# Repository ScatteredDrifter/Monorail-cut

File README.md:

# Monorail V2

This board adapts the original **Monorail V²** however some fundamental changes were made to fit into a different case by **M4NU**.

## Current status:

>Prototypes were ordered and are functioning. 

- + Encoder works 
- + VIAL firmware works 
- + LED-Backlight works
- - misconfigured stabilizer orientation. This has been fixed in 9eb0997

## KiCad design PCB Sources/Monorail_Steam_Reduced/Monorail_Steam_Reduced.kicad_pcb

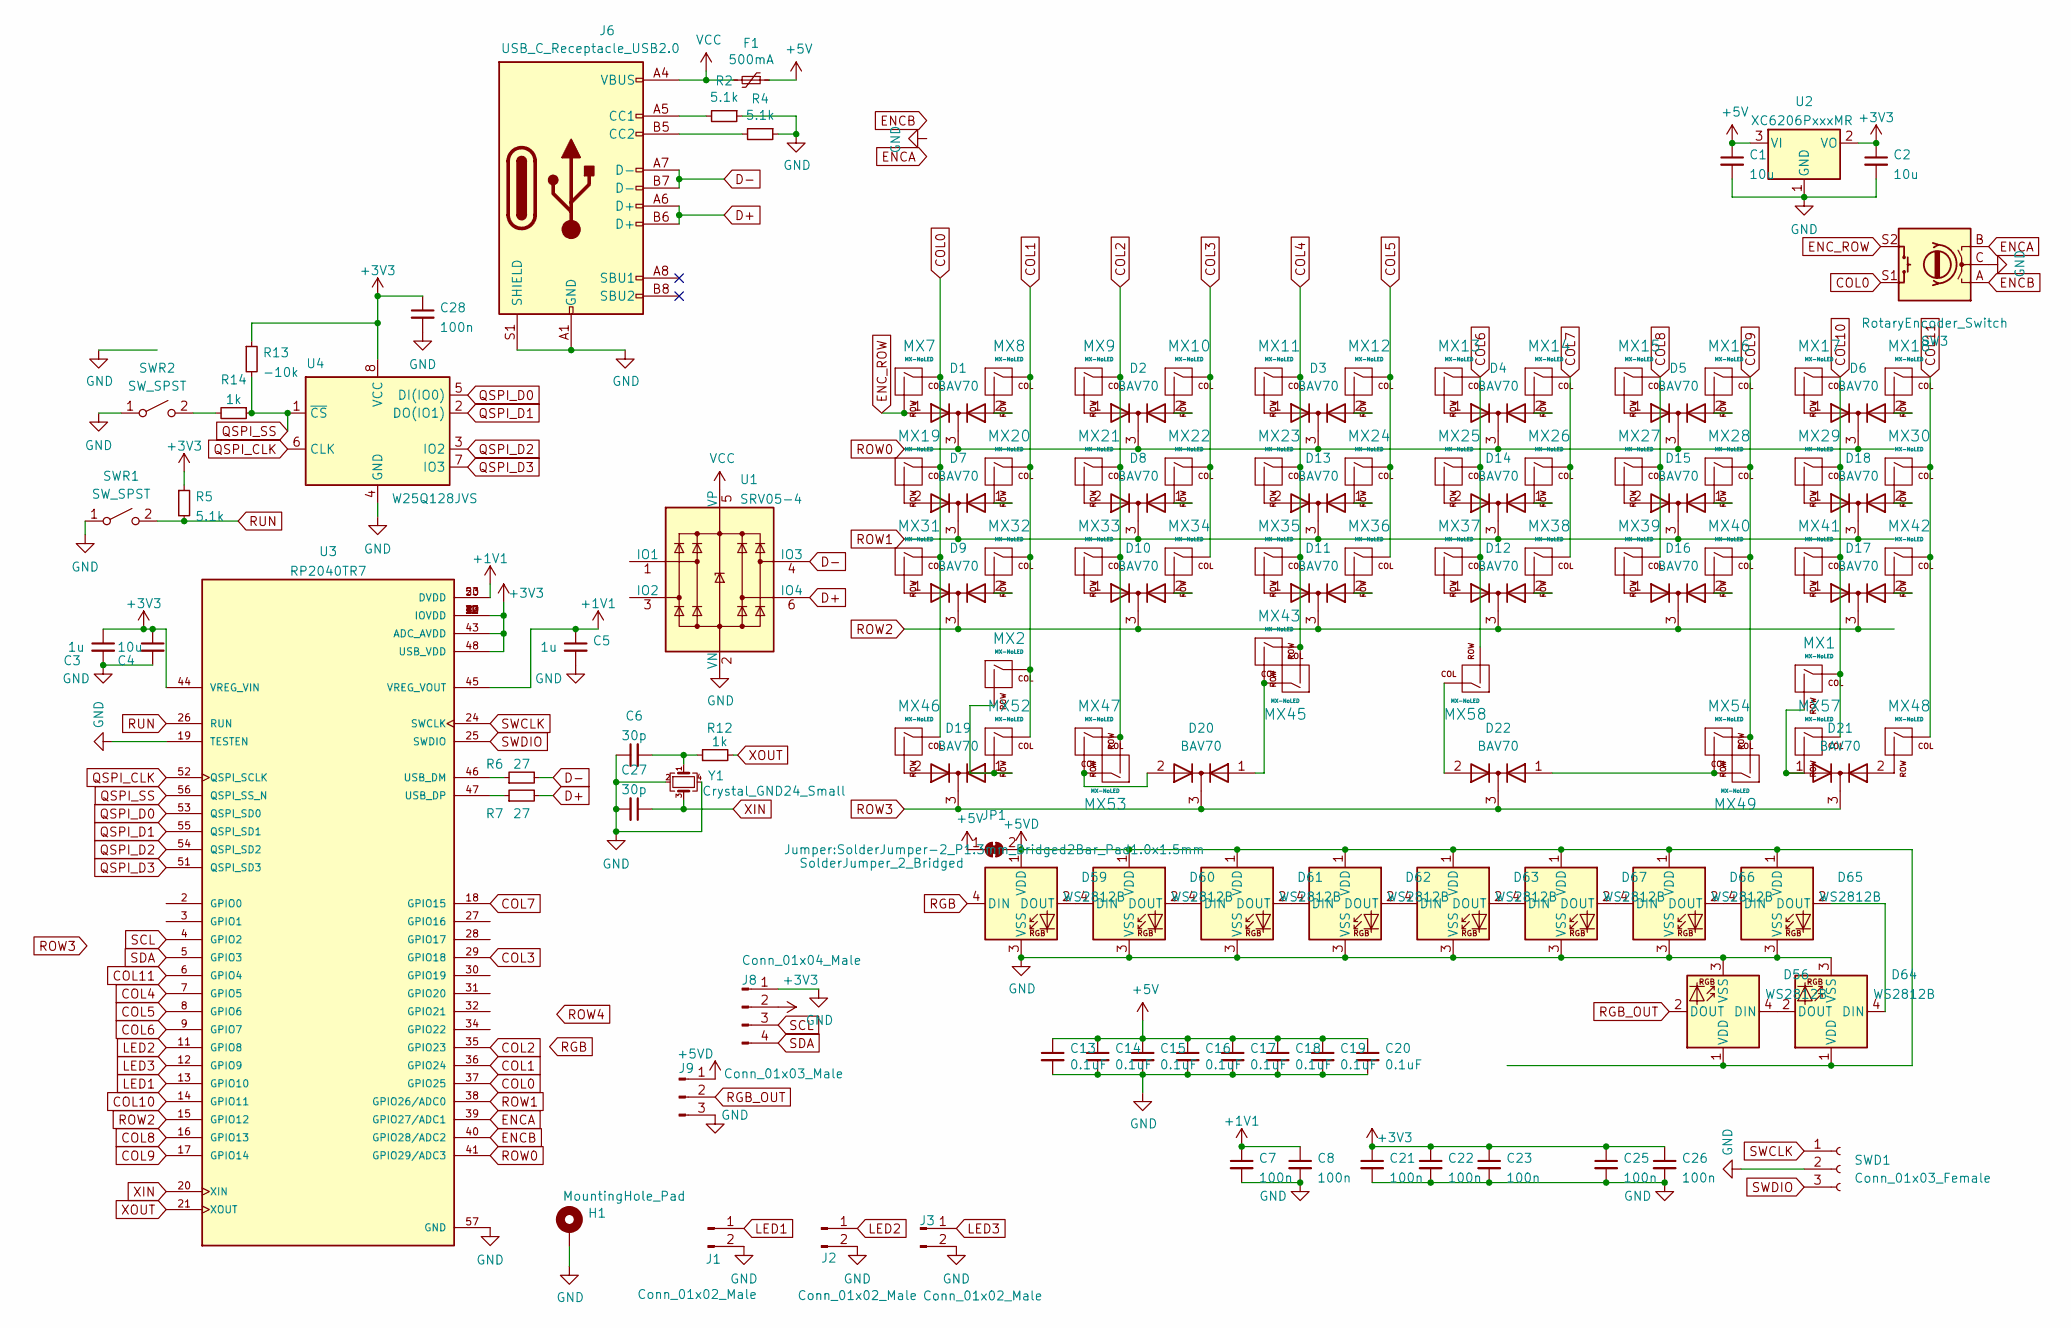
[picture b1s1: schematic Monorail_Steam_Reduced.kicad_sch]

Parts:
C1, C2, C4: 10u; C_0402_1005Metric
C3, C5: 1u; C_0402_1005Metric
C6, C27: 30p; C_0402_1005Metric
C7, C8, C21, C22, C23, C25, C26, C28: 100n; C_0402_1005Metric
C13, C14, C15, C16, C17, C18, C19, C20: 0.1uF; C_0603_1608Metric
D1, D2, D3, D4, D5, D6, D7, D8, D9, D10, D11, D12, D13, D14, D15, D16, D17, D18, D19, D20, D21, D22: BAV70; SOT-23
D56, D59, D60, D61, D62, D63, D64, D65, D66, D67: WS2812B; WS2812B_data-bridgeable
F1: 500mA; Fuse_1206_3216Metric
H1: MountingHole_Pad; Minivan-reference
J1, J2, J3: Conn_01x02_Male; PinHeader_1x02_P2.54mm_Vertical
J6: USB_C_Receptacle_USB2.0; USB_C_Receptacle_HRO_TYPE-C-31-M-12
J8: Conn_01x04_Male; PinHeader_1x04_P2.54mm_Vertical
J9: Conn_01x03_Male; PinHeader_1x03_P2.54mm_Vertical
JP1: SolderJumper_2_Bridged; SolderJumper-2_P1.3mm_Bridged2Bar_Pad1.0x1.5mm
MX1, MX2, MX7, MX8, MX9, MX10, MX11, MX12, MX13, MX14, MX15, MX16, MX17, MX18, MX19, MX20, MX21, MX22, MX23, MX24, MX25, MX26, MX27, MX28, MX29, MX30, MX31, MX32, MX33, MX34, MX35, MX36, MX37, MX38, MX39, MX40, MX41, MX42, MX43, MX45, MX46, MX47, MX48, MX49, MX52, MX53, MX54, MX57, MX58: MX-NoLED; SW_MX_HS_1u_NOREF
R2, R4: 5.1k; R_0603_1608Metric
R5: 5.1k; R_0402_1005Metric
R6, R7: 27; R_0402_1005Metric
R12, R14: 1k; R_0402_1005Metric
R13: -10k; R_0603_1608Metric
SW3: RotaryEncoder_Switch; ROT_Alps_EC11E-Switch
SWD1: Conn_01x03_Female; PinHeader_1x03_P2.54mm_Vertical
SWR1, SWR2: SW_SPST; SW_SPST_TL3342
U1: SRV05-4; SOT-23-6
U2: XC6206PxxxMR; SOT-23
U3: RP2040TR7; RP2040-QFN-56; PARTREV 1.7.1
U4: W25Q128JVS; SOIC-8_5.23x5.23mm_P1.27mm
Y1: Crystal_GND24_Small; Crystal_SMD_3225-4Pin_3.2x2.5mm

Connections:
+1V1: C5.1, C7.1, C8.1, U3.23 (DVDD), U3.45 (VREG_VOUT), U3.50 (DVDD)
+3V3: C2.1, C3.1, C4.1, C21.1, C22.1, C23.1, C25.1, C26.1, C28.1, J8.2, R5.1, R13.1, U2.2 (VO), U3.1 (IOVDD), U3.10 (IOVDD), U3.22 (IOVDD), U3.33 (IOVDD), U3.42 (IOVDD), U3.43 (ADC_AVDD), U3.44 (VREG_VIN), U3.48 (USB_VDD), U3.49 (IOVDD), U4.8 (VCC)
+5V: C1.1, C13.1, C14.1, C15.1, C16.1, C17.1, C18.1, C19.1, C20.1, F1.1, JP1.1 (A), U2.3 (VI)
+5VD: D56.1 (VDD), D59.1 (VDD), D60.1 (VDD), D61.1 (VDD), D62.1 (VDD), D63.1 (VDD), D64.1 (VDD), D65.1 (VDD), D66.1 (VDD), D67.1 (VDD), J9.1, JP1.2 (B)
COL0: MX7.1 (COL), MX19.1 (COL), MX31.1 (COL), MX46.1 (COL), SW3.S1, U3.37 (GPIO25)
COL1: MX2.1 (COL), MX8.1 (COL), MX20.1 (COL), MX32.1 (COL), MX52.1 (COL), U3.36 (GPIO24)
COL2: MX9.1 (COL), MX21.1 (COL), MX33.1 (COL), MX47.1 (COL), MX53.2 (ROW), U3.35 (GPIO23)
COL3: MX10.1 (COL), MX22.1 (COL), MX34.1 (COL), U3.29 (GPIO18)
COL4: MX11.1 (COL), MX23.1 (COL), MX35.1 (COL), MX43.1 (COL), MX45.2 (ROW), U3.7 (GPIO5)
COL5: MX12.1 (COL), MX24.1 (COL), MX36.1 (COL), U3.8 (GPIO6)
COL6: MX13.1 (COL), MX25.1 (COL), MX37.1 (COL), MX58.2 (ROW), U3.9 (GPIO7)
COL7: MX14.1 (COL), MX26.1 (COL), MX38.1 (COL), U3.18 (GPIO15)
COL8: MX15.1 (COL), MX27.1 (COL), MX39.1 (COL), U3.16 (GPIO13)
COL9: MX16.1 (COL), MX28.1 (COL), MX40.1 (COL), MX49.2 (ROW), MX54.1 (COL), U3.17 (GPIO14)
COL10: MX1.1 (COL), MX17.1 (COL), MX29.1 (COL), MX41.1 (COL), MX57.1 (COL), U3.14 (GPIO11)
COL11: MX18.1 (COL), MX30.1 (COL), MX42.1 (COL), MX48.1 (COL), U3.6 (GPIO4)
D+: J6.A6 (D+), J6.B6 (D+), R7.2, U1.6 (IO4)
D-: J6.A7 (D-), J6.B7 (D-), R6.2, U1.4 (IO3)
ENCA: SW3.B, U3.39 (GPIO27/ADC1)
ENCB: SW3.A, U3.40 (GPIO28/ADC2)
ENC_ROW: D1.1 (A), MX7.2 (ROW), SW3.S2
GND: C1.2, C2.2, C3.2, C4.2, C5.2, C6.1, C7.2, C8.2, C13.2, C14.2, C15.2, C16.2, C17.2, C18.2, C19.2, C20.2, C21.2, C22.2, C23.2, C25.2, C26.2, C27.2, C28.2, D56.3 (VSS), D59.3 (VSS), D60.3 (VSS), D61.3 (VSS), D62.3 (VSS), D63.3 (VSS), D64.3 (VSS), D65.3 (VSS), D66.3 (VSS), D67.3 (VSS), H1.1, J1.2, J2.2, J3.2, J6.A1 (GND), J6.A12 (GND), J6.B1 (GND), J6.B12 (GND), J6.S1 (SHIELD), J8.1, J9.3, R2.1, R4.1, SW3.C, SWD1.2, SWR1.1 (A), SWR2.1 (A), U1.2 (VN), U2.1 (GND), U3.19 (TESTEN), U3.57 (GND), U4.4 (GND), Y1.2, Y1.4
LED1: J1.1, U3.13 (GPIO10)
LED2: J2.1, U3.11 (GPIO8)
LED3: J3.1, U3.12 (GPIO9)
unnamed: C6.2, R12.1, Y1.1
unnamed: D56.4 (DIN), D64.2 (DOUT)
unnamed: D59.2 (DOUT), D60.4 (DIN)
unnamed: D60.2 (DOUT), D61.4 (DIN)
unnamed: D61.2 (DOUT), D62.4 (DIN)
unnamed: D62.2 (DOUT), D63.4 (DIN)
unnamed: D63.2 (DOUT), D67.4 (DIN)
unnamed: D64.4 (DIN), D65.2 (DOUT)
unnamed: D65.4 (DIN), D66.2 (DOUT)
unnamed: D66.4 (DIN), D67.2 (DOUT)
unnamed: J6.A5 (CC1), R2.2
unnamed: J6.B5 (CC2), R4.2
unnamed: D21.1 (A), MX1.2 (ROW), MX57.2 (ROW)
unnamed: D19.1 (A), MX2.2 (ROW), MX52.2 (ROW)
unnamed: D1.2 (A), MX8.2 (ROW)
unnamed: D2.1 (A), MX9.2 (ROW)
unnamed: D2.2 (A), MX10.2 (ROW)
unnamed: D3.1 (A), MX11.2 (ROW)
unnamed: D3.2 (A), MX12.2 (ROW)
unnamed: D4.1 (A), MX13.2 (ROW)
unnamed: D4.2 (A), MX14.2 (ROW)
unnamed: D5.1 (A), MX15.2 (ROW)
unnamed: D5.2 (A), MX16.2 (ROW)
unnamed: D6.1 (A), MX17.2 (ROW)
unnamed: D6.2 (A), MX18.2 (ROW)
unnamed: D7.2 (A), MX19.2 (ROW)
unnamed: D7.1 (A), MX20.2 (ROW)
unnamed: D8.2 (A), MX21.2 (ROW)
unnamed: D8.1 (A), MX22.2 (ROW)
unnamed: D13.2 (A), MX23.2 (ROW)
unnamed: D13.1 (A), MX24.2 (ROW)
unnamed: D14.2 (A), MX25.2 (ROW)
unnamed: D14.1 (A), MX26.2 (ROW)
unnamed: D15.2 (A), MX27.2 (ROW)
unnamed: D15.1 (A), MX28.2 (ROW)
unnamed: D18.1 (A), MX29.2 (ROW)
unnamed: D18.2 (A), MX30.2 (ROW)
unnamed: D9.1 (A), MX31.2 (ROW)
unnamed: D9.2 (A), MX32.2 (ROW)
unnamed: D10.1 (A), MX33.2 (ROW)
unnamed: D10.2 (A), MX34.2 (ROW)
unnamed: D11.1 (A), MX35.2 (ROW)
unnamed: D11.2 (A), MX36.2 (ROW)
unnamed: D12.1 (A), MX37.2 (ROW)
unnamed: D12.2 (A), MX38.2 (ROW)
unnamed: D16.1 (A), MX39.2 (ROW)
unnamed: D16.2 (A), MX40.2 (ROW)
unnamed: D17.1 (A), MX41.2 (ROW)
unnamed: D17.2 (A), MX42.2 (ROW)
unnamed: D20.1 (A), MX43.2 (ROW), MX45.1 (COL)
unnamed: D19.2 (A), MX46.2 (ROW)
unnamed: D20.2 (A), MX47.2 (ROW), MX53.1 (COL)
unnamed: D21.2 (A), MX48.2 (ROW)
unnamed: D22.1 (A), MX49.1 (COL), MX54.2 (ROW)
unnamed: D22.2 (A), MX58.1 (COL)
unnamed: R14.2, SWR2.2 (B)
unnamed: R6.1, U3.46 (USB_DM)
unnamed: R7.1, U3.47 (USB_DP)
QSPI_CLK: U3.52 (QSPI_SCLK), U4.6 (CLK)
QSPI_D0: U3.53 (QSPI_SD0), U4.5 (DI(IO0))
QSPI_D1: U3.55 (QSPI_SD1), U4.2 (DO(IO1))
QSPI_D2: U3.54 (QSPI_SD2), U4.3 (IO2)
QSPI_D3: U3.51 (QSPI_SD3), U4.7 (IO3)
QSPI_SS: R13.2, R14.1, U3.56 (QSPI_SS_N), U4.1 (~CS)
RGB: D59.4 (DIN)
RGB_OUT: D56.2 (DOUT), J9.2
ROW0: D1.3 (K), D2.3 (K), D3.3 (K), D4.3 (K), D5.3 (K), D6.3 (K), U3.41 (GPIO29/ADC3)
ROW1: D7.3 (K), D8.3 (K), D13.3 (K), D14.3 (K), D15.3 (K), D18.3 (K), U3.38 (GPIO26/ADC0)
ROW2: D9.3 (K), D10.3 (K), D11.3 (K), D12.3 (K), D16.3 (K), D17.3 (K), U3.15 (GPIO12)
ROW3: D19.3 (K), D20.3 (K), D21.3 (K), D22.3 (K)
RUN: R5.2, SWR1.2 (B), U3.26 (RUN)
SCL: J8.3, U3.4 (GPIO2)
SDA: J8.4, U3.5 (GPIO3)
SWCLK: SWD1.1, U3.24 (SWCLK)
SWDIO: SWD1.3, U3.25 (SWDIO)
VCC: F1.2, J6.A4 (VBUS), J6.A9 (VBUS), J6.B4 (VBUS), J6.B9 (VBUS), U1.5 (VP)
XIN: C27.1, U3.20 (XIN), Y1.3
XOUT: R12.2, U3.21 (XOUT)

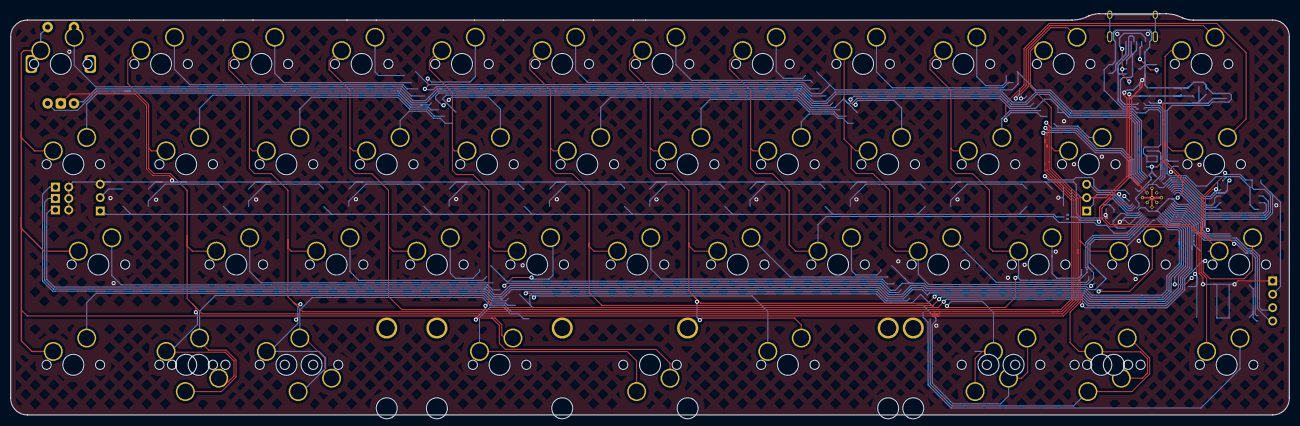
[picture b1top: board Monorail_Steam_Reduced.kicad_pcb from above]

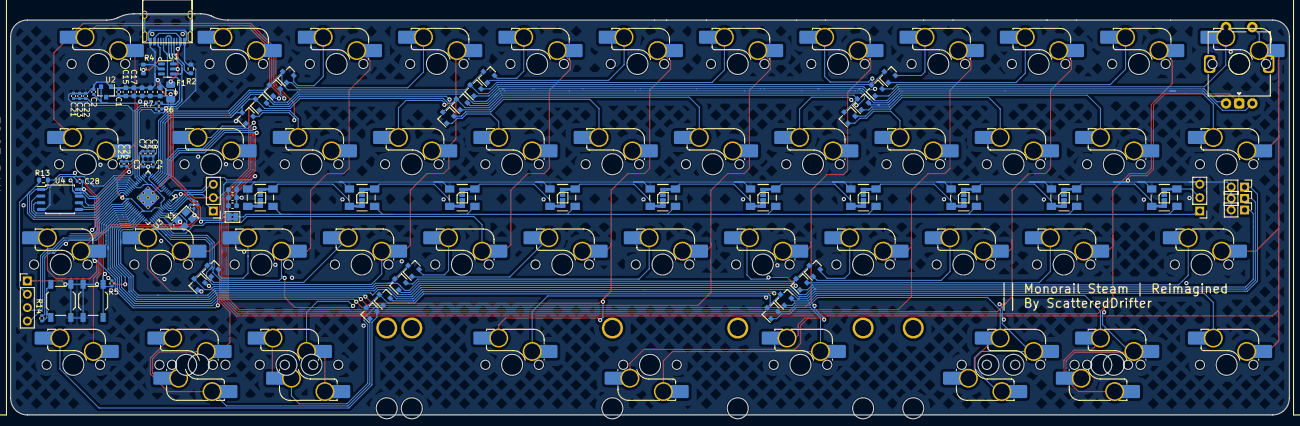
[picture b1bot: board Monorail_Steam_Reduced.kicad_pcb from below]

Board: 2 copper layers, 242.9 x 76.2 mm, 129 parts (129 on the bottom side), 102 nets.

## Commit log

2023-10-15 updated pcb: deleted num-row, new bottom row
2023-10-15 removed unecessary files, cleaned pcb
2023-10-15 updated positions, readme, deleted unecessary files
2023-10-18 set initial positions for components
2023-10-19 began routing upper portion, improved placement
2023-10-21 updated routing, position of diodes
2023-10-21 finished base routing
2023-10-21 added mounting holes
2023-10-21 updated positioning
2023-10-22 added silkscreen, finalized position and routing
2023-10-22 finalized silkscreen and fixed positions
2023-10-22 version¹, updated production files, gerber, dir structure
2023-10-24 fixed overlapping nets near encoder, updated gerber
2023-11-18 fix bottom row stabilizer orientation
2023-11-18 update README, add prototype information
2023-11-27 add precompiled firmware and its source
